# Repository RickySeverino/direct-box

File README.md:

### What is a DI Box? ###

DI (Direct Injection) boxes take an unbalanced, high-impedance instrument signal
and converts it to a balanced, low-impedance signal.
Using a DI Box ensures that the signal is recorded at its best.
Also, it allows you to record a direct guitar signal for use in mixing.

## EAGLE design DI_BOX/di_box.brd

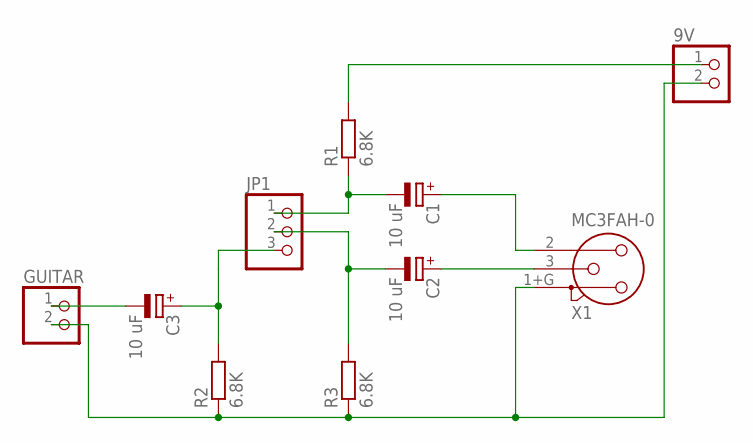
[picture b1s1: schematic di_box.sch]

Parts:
9V: PINHD-1X2; 1X02
C1, C2, C3: 10 uF; E2-4
GUITAR: PINHD-1X2; 1X02
JP1: PINHD-1X3; 1X03
R1, R2, R3: 6.8K; 0207/10
X1: MC3FAH-0; NC3FAH1-0

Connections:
unnamed: C3.+, JP1.3, R2.2
unnamed: C1.-, JP1.1, R1.1
unnamed: 9V.2, GUITAR.2, R2.1, R3.1, X1.1+G (1)
unnamed: C2.-, JP1.2, R3.2
unnamed: C3.-, GUITAR.1
unnamed: 9V.1, R1.2
unnamed: C2.+, X1.3
unnamed: C1.+, X1.2

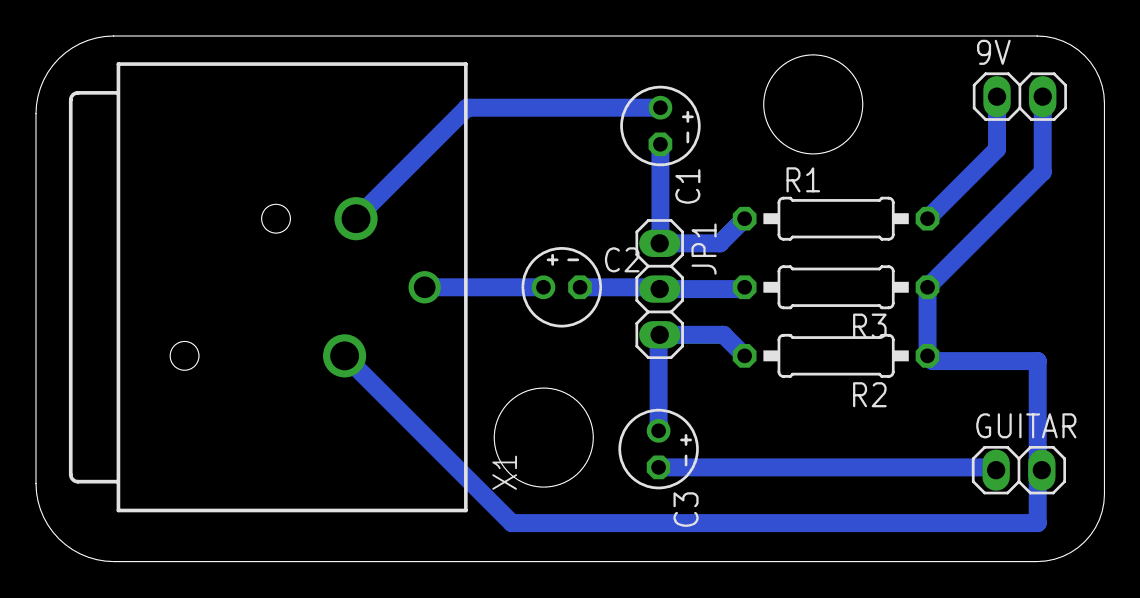
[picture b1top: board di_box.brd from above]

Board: 2 copper layers, 59.4 x 29.2 mm, 10 parts (0 on the bottom side), 8 nets.

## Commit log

2018-08-20 adds .sch and .brd files
2018-08-20 updates readme
2018-08-20 spell check
2019-01-28 updated schematic
